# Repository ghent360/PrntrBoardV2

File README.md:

PrntrBoard V2
======================
PrntrBoard V2 is the next iteration of my 3D printer controller design. The V1 was very good, except it had one major drawback - the stepper drivers were soldered on the board which would make the design expensive.
This V2 design has 6 replaceable motor drivers. While traditional RAMPS based boards use pin headers to house the driver boards, I'm using PCIe 1x slots. This design has several advantages:
  + the driver PCB layout can be more flexible as there are fewer constraints on the driver board dimensions
  + drivers are placed vertically on the board which allows for more efficient space utilization as well as more efficient cooling
  + PCIe 1x slots have 36 pins which allows for greater design flexibility

Project Status
-----
The following functionality has been verified on the rev1 prototype board with Marlin firmware:
  + TMC2660 and TMC2209 drivers working and able to move motors
  + Endstops
  + Heaters and thermistor inputs
  + LCD interface with 12864 panel from FYSETC and REPRAP Discount Graphics Panel.
  + Micro SD-card interface
  + EEPROM
  + Fan control

Features of the board:
-----
  + up to 6x replaceable stepper motor drivers
  + 32-bit Arm processor with floating point support running at 168MHz (STM32F407)
  + up to 6 thermistors or 6 thermocouples for temperature control
  + 4 power heaters (1 bed and up to 3 extruder heaters) with PWM power control
  + 5 low power PWM connectors with selectable voltage (5V vs 12-24V) for fans or LEDs
  + 8 end stops with option to use stall detection from the stepper drivers on 6 of them
  + micro-sd card support with SDIO for fast file transfer
  + 2 extra serial ports for WiFi and or smart LCD screen control
  + RAMPS LCD screen support
  + Marlin 2.0 firmware or Smoothieware V1.0, RRF port in progress, Klipper port in progress.
  + 4 extra fan connectors (2x5V and 2x12-24V)
  + Input voltage: 12-24V
  + CAN bus connector contributed by ArkadiuszRaj.

Drivers
------
High power driver using Trinamic TMC2660. Should support up to 2.5A RMS current per phase with forced cooling. Supports stall detection. Driver current is adjustable via SPI.

Versatile "economy" driver using Trinamic TMC2209. Should support up to 1.8A RMS current per phase with forced cooling. Supports stall detection. Driver current is adjustable via UART.

High voltage driver (up to 42V) using Trinamic TMC2130. Should support up to 1.1A RMS current per phase with forced cooling. Supports stall detection. Driver current is adjustable via SPI. The driver board has separate power terminal.

Very high current driver design using TMC5161 and TMC2160 with external MOSFETS are also possible. In addition an adapter board for Pololu style stepper drivers is planned for backwards compatibility with old drivers.

Software
------

Marlin v2 is working on the board. I have a port of Smoothieware V1. Klipper is functional with some [fixes] (https://github.com/ghent360/klipper). RepRepFirmware ports is in early stages and not yet functional.

Visit [my blog](https://blog.pcbxprt.com/) for status updates on the development of the board.

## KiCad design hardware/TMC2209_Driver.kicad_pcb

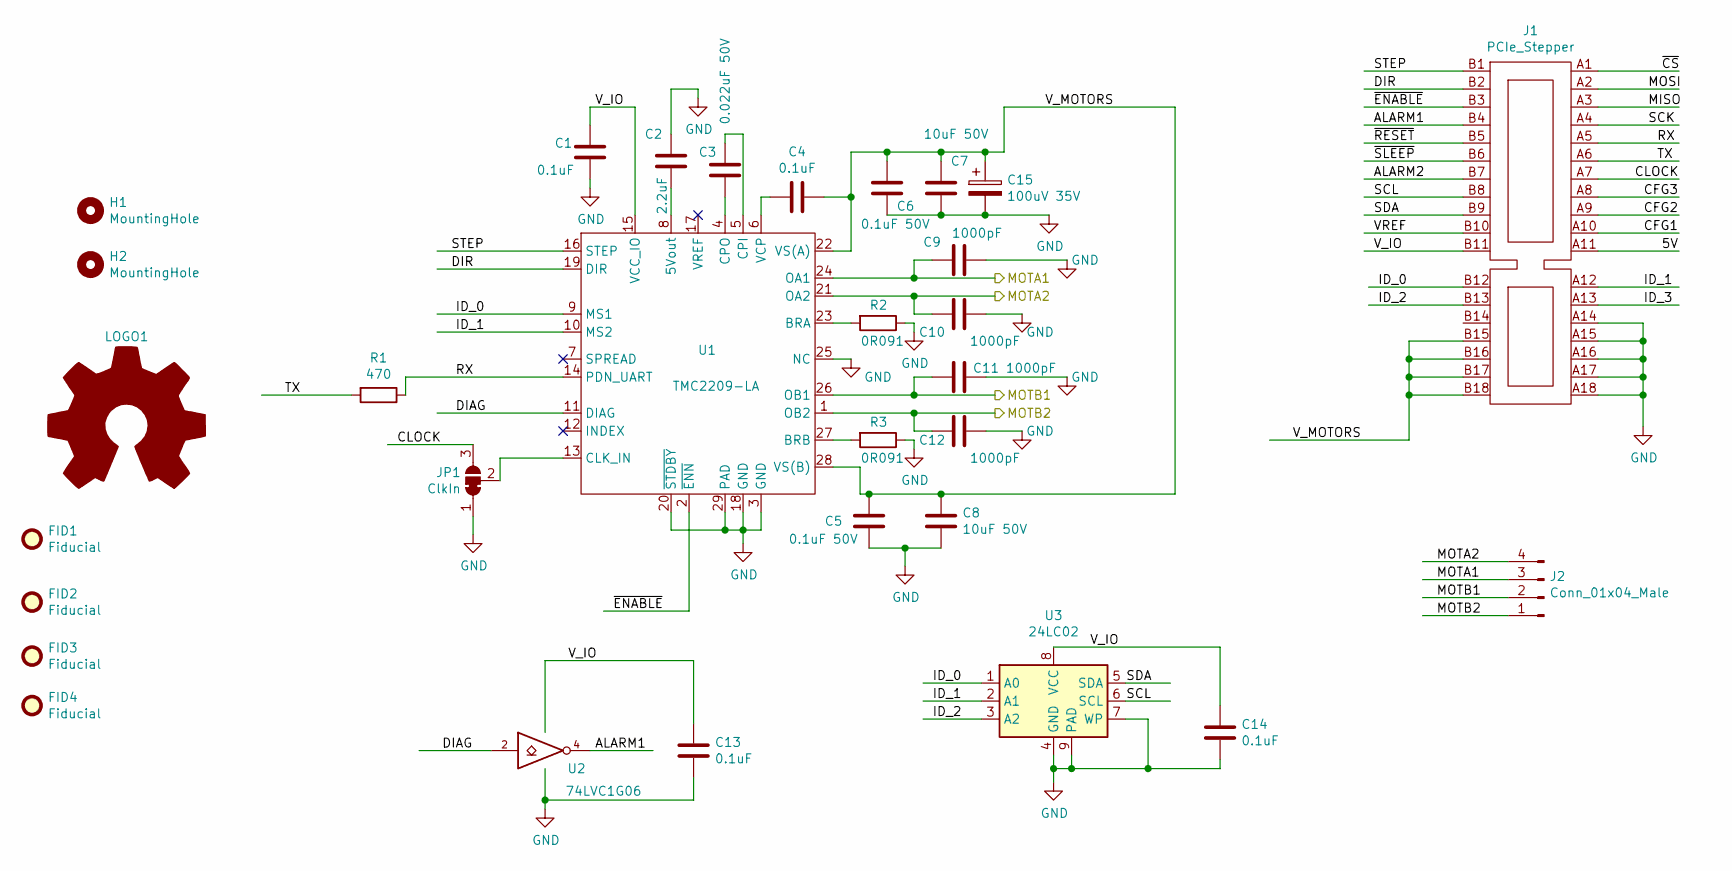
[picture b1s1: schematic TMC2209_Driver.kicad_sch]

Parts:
C1, C4, C13, C14: 0.1uF; C_0603_1608Metric; Part # CC0603KRX7R9BB104; LCSC Part # C14663
C2: 2.2uF; C_0603_1608Metric; Part # CL10A225KO8NNNC; LCSC Part # C23630
C3: 0.022uF 50V; C_0603_1608Metric; Part # CL10B223KB8NNNC; LCSC Part # C21122
C5, C6: 0.1uF 50V; C_0402_1005Metric; Part # CL05B104KO5NNNC; LCSC Part # C1525
C7, C8: 10uF 50V; C_1206_3216Metric; Part # CL31A106KBHNNNE; LCSC Part # C13585
C9, C10, C11, C12: 1000pF; C_0603_1608Metric; Part # CL10B102KB8NNNC; LCSC Part # C1588
C15: 100uV 35V; CP_Elec_6.3x7.7; Part # VE-101M1VTR-0607; LCSC Part # C171732
FID1, FID2, FID3, FID4: Fiducial; Fiducial_1mm_Dia_2.54mm_Outer_CopperTop
H1, H2: MountingHole; MountingHole_2.7mm_M2.5
J1: PCIe_Stepper; BUS_PCIexpress
J2: Conn_01x04_Male; Molex-SL-4POS
JP1: ClkIn; SolderJumper-3_P1.3mm_Bridged12_Pad1.0x1.5mm
LOGO1: Logo_Open_Hardware_Large; OSHW-Logo2_7.3x6mm_SilkScreen
R1: 470; R_0603_1608Metric; Part # 0603WAF4700T5E; LCSC Part # C23179
R2, R3: 0R091; R_1210_3225Metric; Part # 1206W3F910MT5E; LCSC Part # C247542
U1: TMC2209-LA; TMC22xx_QFN; Part # TMC2209-LA; LCSC Part # C465949
U2: 74LVC1G06; SOT-353_SC-70-5; Part # 74LVC1G06GW,125; LCSC Part # C426704
U3: 24LC02; TDFN-8-1EP_3x2mm_P0.5mm_EP1.56x1.45mm; Part # CAT24C02VP2IGT3A; LCSC Part # C184154

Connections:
/5V: J1.A11
/ALARM1: J1.B4, U2.4
/ALARM2: J1.B7
/CFG1: J1.A10
/CFG2: J1.A9
/CFG3: J1.A8
/CLOCK: J1.A7, JP1.3 (B)
/DIAG: U1.11 (DIAG), U2.2
/DIR: J1.B2, U1.19 (DIR)
/ID_0: J1.B12, U1.9 (MS1), U3.1 (A0)
/ID_1: J1.A12, U1.10 (MS2), U3.2 (A1)
/ID_2: J1.B13, U3.3 (A2)
/ID_3: J1.A13
/MISO: J1.A3
/MOSI: J1.A2
/MOTA1: C9.2, J2.3, U1.24 (OA1)
/MOTA2: C10.2, J2.4, U1.21 (OA2)
/MOTB1: C11.2, J2.2, U1.26 (OB1)
/MOTB2: C12.2, J2.1, U1.1 (OB2)
/RX: J1.A5, R1.1, U1.14 (PDN_UART)
/SCK: J1.A4
/SCL: J1.B8, U3.6 (SCL)
/SDA: J1.B9, U3.5 (SDA)
/STEP: J1.B1, U1.16 (STEP)
/TX: J1.A6, R1.2
/VREF: J1.B10
/V_MOTORS: C4.1, C5.1, C6.1, C7.1, C8.1, C15.1, J1.B15, J1.B16, J1.B17, J1.B18, U1.22 (VS(A)), U1.28 (VS(B))
/~CS: J1.A1
/~ENABLE: J1.B3, U1.2 (~ENN)
/~RESET: J1.B5
/~SLEEP: J1.B6
GND: C1.2, C2.1, C5.2, C6.2, C7.2, C8.2, C9.1, C10.1, C11.1, C12.1, C13.2, C14.2, C15.2, J1.A14, J1.A15, J1.A16, J1.A17, J1.A18, JP1.1 (A), R2.1, R3.1, U1.3 (GND), U1.18 (GND), U1.20 (~STDBY), U1.25 (NC), U1.29 (PAD), U2.3 (GND), U3.4 (GND), U3.7 (WP), U3.9 (PAD)
unnamed: C2.2, U1.8 (5Vout)
unnamed: C3.1, U1.5 (CPI)
unnamed: C3.2, U1.4 (CPO)
unnamed: C4.2, U1.6 (VCP)
unnamed: JP1.2 (C), U1.13 (CLK_IN)
unnamed: R2.2, U1.23 (BRA)
unnamed: R3.2, U1.27 (BRB)
VCC: C1.1, C13.1, C14.1, J1.B11, U1.15 (VCC_IO), U2.5 (VCC), U3.8 (VCC)

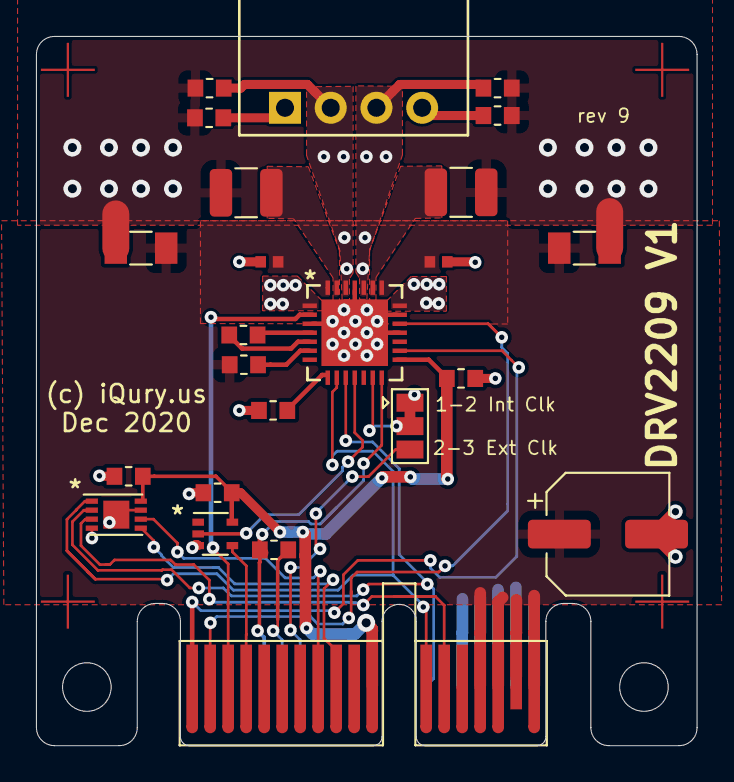
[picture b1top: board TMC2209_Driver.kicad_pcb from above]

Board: 2 copper layers, 36.7 x 39.4 mm, 31 parts (1 on the bottom side), 27 nets.

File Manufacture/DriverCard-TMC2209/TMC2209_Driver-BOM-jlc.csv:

Comment,Designator,Footprint,LCSC, LCSC Part #, Part #
"0.1uF","C1,C4,C13,C14","PrntrBoardV2:C_0603_1608Metric","","C14663","CC0603KRX7R9BB104"
"100uV 35V","C15","Capacitor_SMD:CP_Elec_6.3x7.7","","C171732","VE-101M1VTR-0607"
"2.2uF","C2","PrntrBoardV2:C_0603_1608Metric",""," C23630","CL10A225KO8NNNC"
"0.022uF 50V","C3","PrntrBoardV2:C_0603_1608Metric","","C21122","CL10B223KB8NNNC"
"0.1uF 50V","C5,C6","PrntrBoardV2:C_0402_1005Metric","","C1525","CL05B104KO5NNNC"
"10uF 50V","C7,C8","PrntrBoardV2:C_1206_3216Metric","","C13585","CL31A106KBHNNNE"
"1000pF","C9,C10,C11,C12","PrntrBoardV2:C_0603_1608Metric","","C1588","CL10B102KB8NNNC"
"Conn_01x04_Male","J2","PrntrBoardV2:Molex-SL-4POS",""
"470","R1","PrntrBoardV2:R_0603_1608Metric","","C23179","0603WAF4700T5E"
"0R091","R2,R3","Resistor_SMD:R_1210_3225Metric","","C247542","1206W3F910MT5E"
"TMC2209-LA","U1","PrntrBoardV2:TMC22xx_QFN","","C465949","TMC2209-LA"
"74LVC1G06","U2","Package_TO_SOT_SMD:SOT-353_SC-70-5","","C426704","74LVC1G06GW,125"
"24LC02","U3","PrntrBoardV2:TDFN-8-1EP_3x2mm_P0.5mm_EP1.56x1.45mm","","C184154","CAT24C02VP2IGT3A"

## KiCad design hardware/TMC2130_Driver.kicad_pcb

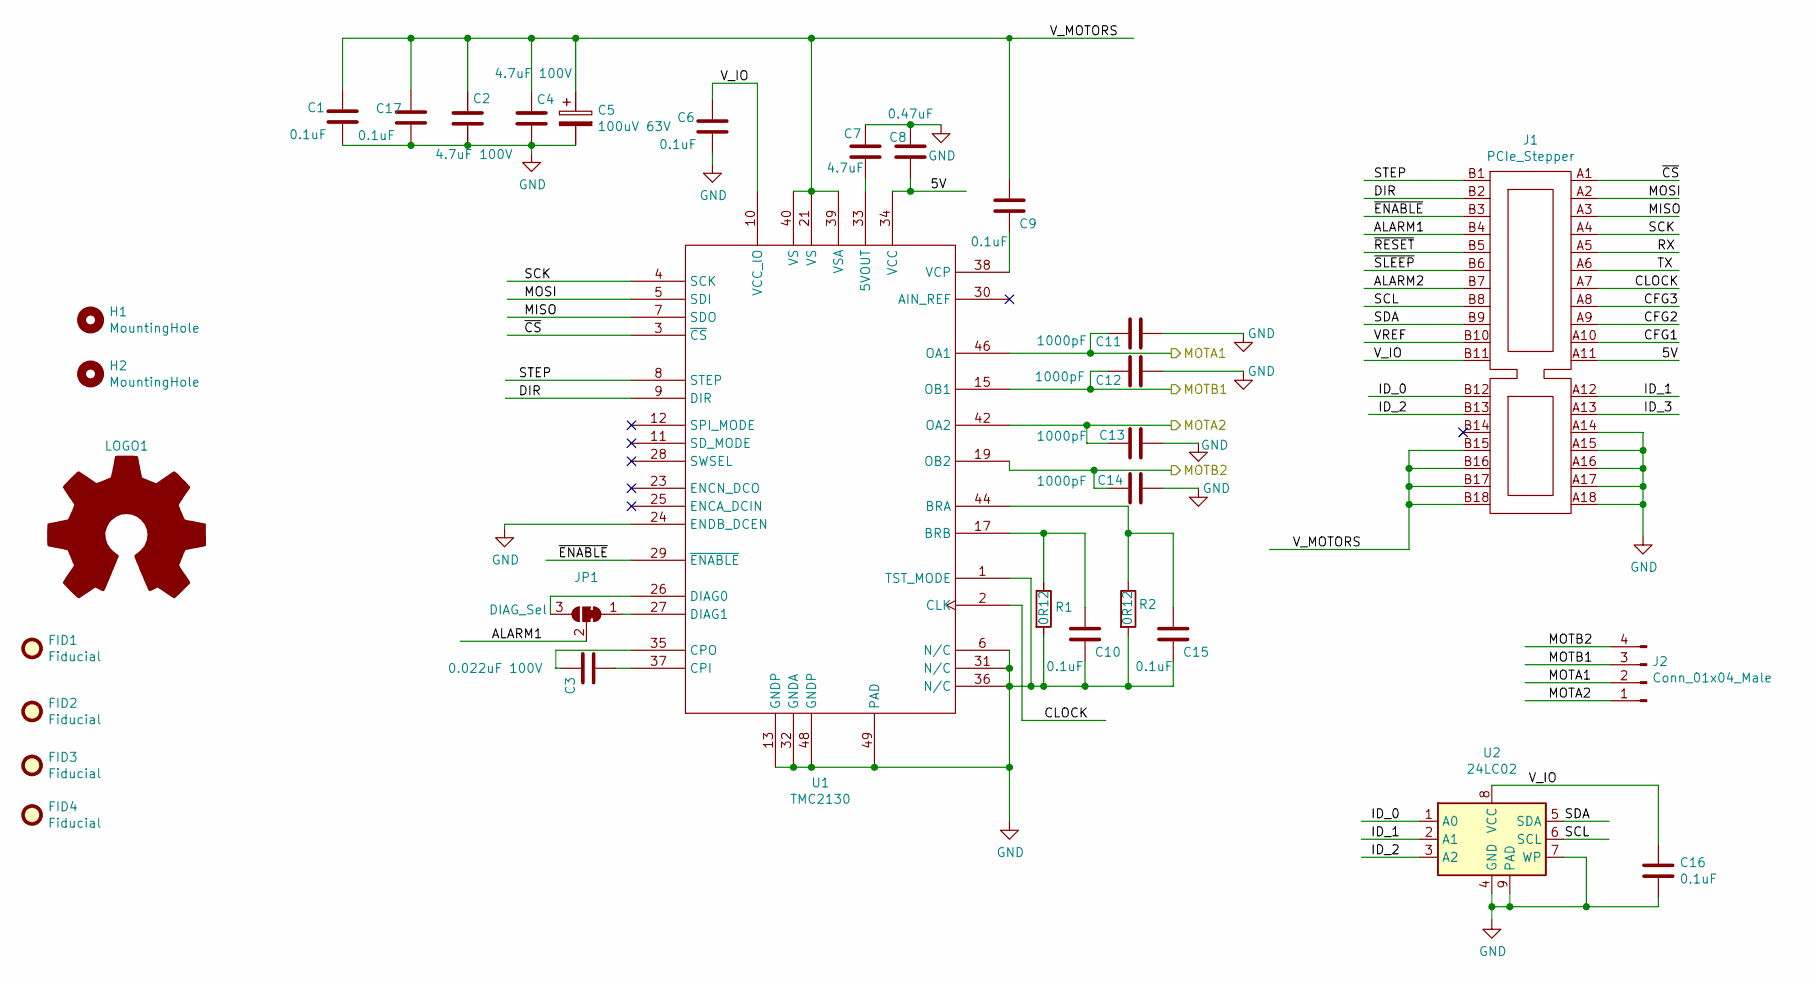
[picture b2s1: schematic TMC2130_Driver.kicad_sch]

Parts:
C1, C9, C17: 0.1uF; C_0805_2012Metric; Part # CL21B104KCFNNNE; LCSC Part # C28233
C2, C4: 4.7uF 100V; C_1210_3225Metric; Part # HMK325C7475KN-TE; LCSC Part # C697607
C3: 0.022uF 100V; C_0805_2012Metric; Part # CC0603KRX7R0BB223; LCSC Part # C313105
C5: 100uV 63V; CP_Elec_10x10.5; Part # CK1J101MCRG10; LCSC Part # C263945
C6, C16: 0.1uF; C_0603_1608Metric; Part # CC0603KRX7R9BB104; LCSC Part # C14663
C7: 4.7uF; C_0603_1608Metric; Part # CL10A475KO8NNNC; LCSC Part # C19666
C8: 0.47uF; C_0603_1608Metric; Part # CL10B474KA8NNNC; LCSC Part # C1623
C10, C15: 0.1uF; C_0805_2012Metric; Part # HMK325C7475KN-TE; LCSC Part # C28233
C11, C12, C13, C14: 1000pF; C_0603_1608Metric; Part # CL10B102KC8NNNC; LCSC Part # C153291
FID1, FID2, FID3, FID4: Fiducial; Fiducial_1mm_Dia_2.54mm_Outer_CopperTop
H1, H2: MountingHole; MountingHole_2.7mm_M2.5
J1: PCIe_Stepper; BUS_PCIexpress
J2: Conn_01x04_Male; Molex-SL-4POS
JP1: DIAG_Sel; SolderJumper-3_P1.3mm_Bridged12_Pad1.0x1.5mm
LOGO1: Logo_Open_Hardware_Large; OSHW-Logo2_7.3x6mm_SilkScreen
R1, R2: 0R12; R_2512_6332Metric; Part # 25121WF120LT4E; LCSC Part # C81248
U1: TMC2130; tmc5130-nc; Part # TMC2130A-TA; LCSC Part # C328952
U2: 24LC02; TDFN-8-1EP_3x2mm_P0.5mm_EP1.56x1.45mm; Part # CAT24C02VP2IGT3A; LCSC Part # C184154

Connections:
/5V: C8.1, J1.A11, U1.34 (VCC)
/ALARM1: J1.B4, JP1.2 (C)
/ALARM2: J1.B7
/CFG1: J1.A10
/CFG2: J1.A9
/CFG3: J1.A8
/CLOCK: J1.A7, U1.2 (CLK)
/DIR: J1.B2, U1.9 (DIR)
/ID_0: J1.B12, U2.1 (A0)
/ID_1: J1.A12, U2.2 (A1)
/ID_2: J1.B13, U2.3 (A2)
/ID_3: J1.A13
/MISO: J1.A3, U1.7 (SDO)
/MOSI: J1.A2, U1.5 (SDI)
/MOTA1: C11.2, J2.2, U1.46 (OA1)
/MOTA2: C13.2, J2.1, U1.42 (OA2)
/MOTB1: C12.2, J2.3, U1.15 (OB1)
/MOTB2: C14.2, J2.4, U1.19 (OB2)
/RX: J1.A5
/SCK: J1.A4, U1.4 (SCK)
/SCL: J1.B8, U2.6 (SCL)
/SDA: J1.B9, U2.5 (SDA)
/STEP: J1.B1, U1.8 (STEP)
/TX: J1.A6
/VREF: J1.B10
/V_IO: C6.1, C16.1, J1.B11, U1.10 (VCC_IO), U2.8 (VCC)
/V_MOTORS: C1.1, C2.1, C4.1, C5.1, C9.1, C17.1, J1.B15, J1.B16, J1.B17, J1.B18, U1.21 (VS), U1.39 (VSA), U1.40 (VS)
/~CS: J1.A1, U1.3 (~CS)
/~ENABLE: J1.B3, U1.29 (~ENABLE)
/~RESET: J1.B5
/~SLEEP: J1.B6
GND: C1.2, C2.2, C4.2, C5.2, C6.2, C7.1, C8.2, C10.2, C11.1, C12.1, C13.1, C14.1, C15.2, C16.2, C17.2, J1.A14, J1.A15, J1.A16, J1.A17, J1.A18, R1.2, R2.2, U1.1 (TST_MODE), U1.6 (N/C), U1.13 (GNDP), U1.24 (ENDB_DCEN), U1.31 (N/C), U1.32 (GNDA), U1.36 (N/C), U1.48 (GNDP), U1.49 (PAD), U2.4 (GND), U2.7 (WP), U2.9 (PAD)
unnamed: C3.1, U1.35 (CPO)
unnamed: C3.2, U1.37 (CPI)
unnamed: C7.2, U1.33 (5VOUT)
unnamed: C9.2, U1.38 (VCP)
unnamed: C10.1, R1.1, U1.17 (BRB)
unnamed: C15.1, R2.1, U1.44 (BRA)
unnamed: JP1.1 (A), U1.27 (DIAG1)
unnamed: JP1.3 (B), U1.26 (DIAG0)

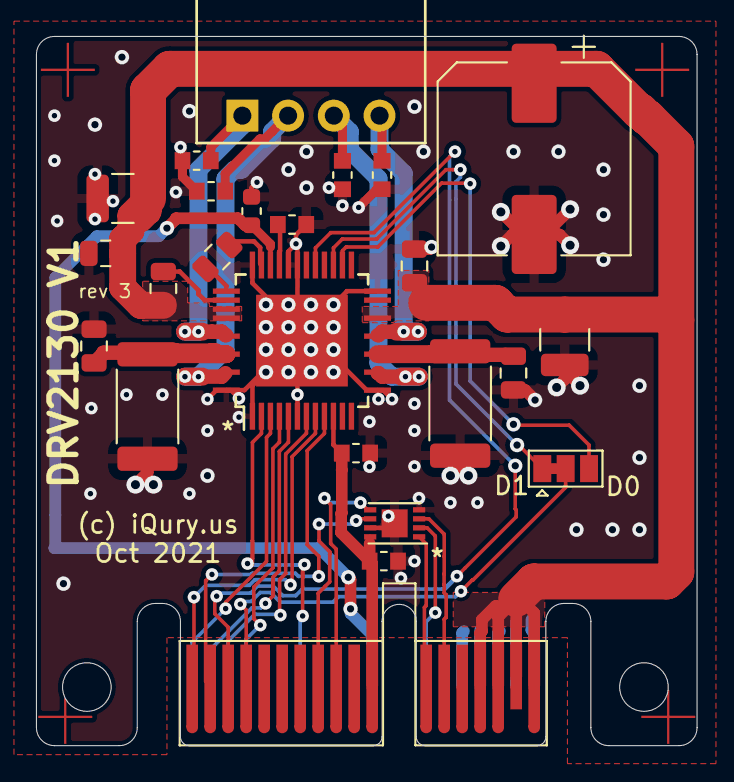
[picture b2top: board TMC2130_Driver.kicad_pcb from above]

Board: 2 copper layers, 36.7 x 39.4 mm, 31 parts (1 on the bottom side), 30 nets.

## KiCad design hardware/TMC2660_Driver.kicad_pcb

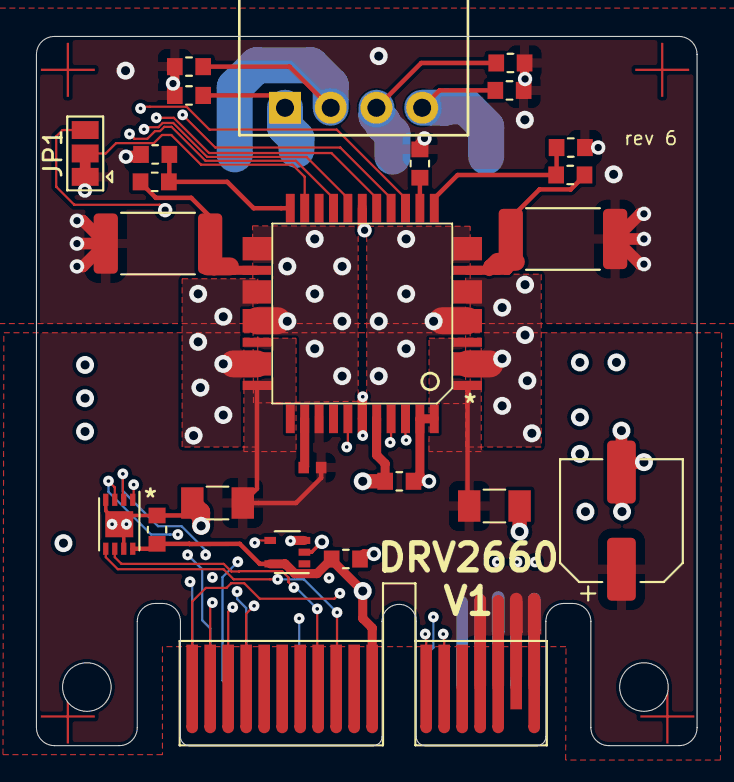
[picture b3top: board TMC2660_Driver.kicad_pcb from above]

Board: 4 copper layers, 36.7 x 39.4 mm, 31 parts (1 on the bottom side), 29 nets.

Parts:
C1, C2: 10uF 50V; C_1206_3216Metric
C3, C6, C14: 0.1uF; C_0603_1608Metric
C4: 0.1uF 50V; C_0402_1005Metric
C5: 0.47uF; C_0603_1608Metric
C7, C12: 0.01uF; C_0603_1608Metric
C8, C9, C10, C11: 1000pF; C_0603_1608Metric
C13: 100uF 35V; CP_Elec_6.3x7.7
FID1, FID2, FID3, FID4: Fiducial; Fiducial_1mm_Dia_2.54mm_Outer_CopperTop
H1, H2: MountingHole; MountingHole_2.7mm_M2.5
J1: PCIe_Stepper; BUS_PCIexpress
J2: Conn_01x04_Male; Molex-SL-4POS
JP1: ClkIn; SolderJumper-3_P1.3mm_Bridged12_Pad1.0x1.5mm
LOGO1: Logo_Open_Hardware_Large; OSHW-Logo2_7.3x6mm_SilkScreen
R1, R3: 22R; R_0603_1608Metric
R2, R4: 0R051; R_2512_6332Metric
U1: TMC2660
U2: 74LVC1G06; SOT-353_SC-70-5
U3: 24LC02; TDFN-8-1EP_3x2mm_P0.5mm_EP1.56x1.45mm

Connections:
/ALARM1: J1.B4, U2.4
/CLOCK: J1.A7, JP1.3 (B)
/DIAG: U1.38 (SG_TST), U2.2
/DIR: J1.B2, U1.41 (DIR)
/ID_0: J1.B12, U3.1 (A0)
/ID_1: J1.A12, U3.2 (A1)
/ID_2: J1.B13, U3.3 (A2)
/MISO: J1.A3, U1.15 (SDI)
/MOSI: J1.A2, U1.14 (SDO)
/MOTA1: C8.2, J2.4, U1.2.3 (OA1), U1.7.8 (OA1)
/MOTA2: C9.2, J2.3, U1.5.6 (OA2), U1.10.1 (OA2)
/MOTB1: C10.2, J2.2, U1.26.7 (OB1), U1.31.2 (OB1)
/MOTB2: C11.2, J2.1, U1.23.4 (OB2), U1.28.9 (OB2)
/SCK: J1.A4, U1.16 (SCK)
/SCL: J1.B8, U3.6 (SCL)
/SDA: J1.B9, U3.5 (SDA)
/STEP: J1.B1, U1.42 (STEP)
/V_MOTORS: C1.1, C2.1, C4.1, C13.1, J1.B15, J1.B16, J1.B17, J1.B18, U1.1 (NC), U1.4 (VSA), U1.30 (VSB), U1.33 (NC), U1.36 (VS)
/~CS: J1.A1, U1.18 (~CS)
/~ENABLE: J1.B3, U1.19 (~EN)
GND: C1.2, C2.2, C3.2, C5.1, C6.2, C7.2, C8.1, C9.1, C10.1, C11.1, C12.2, C13.2, C14.2, J1.A14, J1.A15, J1.A16, J1.A17, J1.A18, JP1.1 (A), R2.2, R4.2, U1.17 (GND), U1.39 (GND), U1.43 (TST_MODE), U1.44 (GND), U2.3 (GND), U3.4 (GND), U3.7 (WP), U3.9 (PAD)
unnamed: C4.2, U1.35 (VHS)
unnamed: C5.2, U1.13 (5VOUT)
unnamed: C7.1, R1.1, U1.22 (SRB)
unnamed: C12.1, R3.1, U1.12 (SRA)
unnamed: R1.2, R2.1, U1.25 (BRB)
unnamed: R3.2, R4.1, U1.9 (BRA)
unnamed: JP1.2 (C), U1.21 (CLK)
VCC: C3.1, C6.1, C14.1, J1.B11, U1.40 (VCC_IO), U2.5 (VCC), U3.8 (VCC)

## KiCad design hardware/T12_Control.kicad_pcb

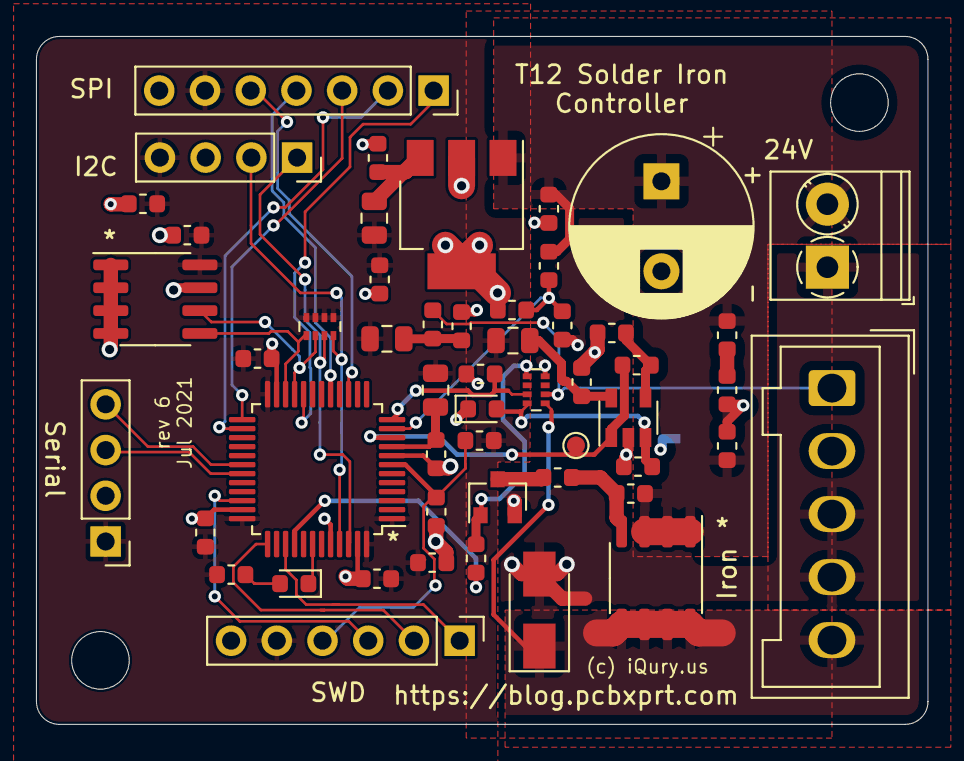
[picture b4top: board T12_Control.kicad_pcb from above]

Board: 4 copper layers, 49.5 x 38.2 mm, 55 parts (1 on the bottom side), 37 nets.

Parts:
C1, C2, C3, C4, C6, C7, C8, C9, C11, C13, C14, C17: 100nF; C_0603_1608Metric
C5: 10uF; C_0603_1608Metric
C10, C18: 10nF; C_0603_1608Metric
C12: 100uF 35V; CP_Radial_D10.0mm_P5.00mm
C15: 1nF; C_0603_1608Metric
C16: 470pF; C_0603_1608Metric
C19: 1uF; C_0603_1608Metric
D1: RS1M; D_SMA
D2, D3: RED; LED_0603_1608Metric
FB1, FB2, FB3, FB4: Ferrite_Bead; L_0805_2012Metric
H1, H2: MountingHole; MountingHole_3.2mm_M3_DIN965
J1: Screw_Terminal_01x02; TerminalBlock_Phoenix_PT-1,5-2-3.5-H_1x02_P3.50mm_Horizontal
J2: GX12-5M; Wago_734-135_1x05_P3.50mm_Vertical
J3: SPI LCD; PinSocket_1x07_P2.54mm_Vertical
J4: I2C LCD; PinSocket_1x04_P2.54mm_Vertical
J5: SWD; PinHeader_1x06_P2.54mm_Vertical
J6: Serial; PinHeader_1x04_P2.54mm_Vertical
NT1: Net-Tie_2; NetTie-2_SMD_Pad0.5mm
Q1: TPC8107; SO-8_3.9x4.9mm_P1.27mm
Q2: BC817; SOT-23
R1: 2k; R_0603_1608Metric
R2, R7: 10k; R_0603_1608Metric
R3, R4, R9: 1k; R_0603_1608Metric
R5: 1k 0.1%; R_0603_1608Metric
R6: 249k 0.1%; R_0603_1608Metric
R8: 470; R_0603_1608Metric
R10: 2.2; R_0603_1608Metric
R11: 4.7k 1%; R_0603_1608Metric
RN1, RN2: 4x4.7k; R_Array_Concave_4x0402
TP1: TestPoint; TestPoint_Pad_D1.0mm
U1: SPX2954M3-3.3_SOT223; SOT-223-3_TabPin2
U2: 24LC32; SOIC-8_3.9x4.9mm_P1.27mm
U3: SGM8551XN; SOT-23-5
U4: STM32F103CBTx; LQFP-48_7x7mm_P0.5mm

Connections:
/3.3V: C3.1, C6.1, C7.1, C8.1, C9.1, C14.1, C17.1, FB1.2, FB2.1, FB3.1, FB4.1, J3.6, J4.4, J5.5, J6.1, R7.1, R9.2, RN2.1 (R1.1), RN2.2 (R2.1), RN2.3 (R3.1), RN2.4 (R4.1), U2.8 (VCC), U4.1 (VBAT), U4.24 (VDD), U4.36 (VDD), U4.48 (VDD)
/24V: C1.1, C2.1, C12.1, J1.2, Q1.1 (S), Q1.2 (S), Q1.3 (S), R1.1, R2.1, R10.1, U1.1 (VI)
/D/~C: J3.2, U4.26 (PB13)
/EE_SCL: RN2.6 (R3.2), U2.6 (SCL), U4.21 (PB10)
/EE_SDA: RN2.5 (R4.2), U2.5 (SDA), U4.22 (PB11)
/HEATER_ON: R8.2, U4.40 (PB4)
/MOSI: J3.4, U4.17 (PA7)
/NTC: C19.1, RN1.3 (R3.1), U4.12 (PA2)
/OLED_SCL: J4.2, RN2.8 (R1.2), U4.45 (PB8)
/OLED_SDA: J4.1, RN2.7 (R2.2), U4.46 (PB9)
/RX: J6.3, U4.31 (PA10)
/SCK: J3.5, U4.15 (PA5)
/SWDCLK: J5.2, U4.37 (PA14)
/SWDIO: J5.3, U4.34 (PA13)
/SWDSWO: J5.1, U4.39 (PB3)
/TIP_TEMP: R6.2, TP1.1, U3.1, U4.10 (PA0)
/TX: J6.4, U4.30 (PA9)
/V_MON: C4.1, R2.2, R4.1, U4.11 (PA1)
/~CS: J3.1, U4.20 (PB2)
/~NRST: C11.2, J5.4, R7.2, U4.7 (NRST)
/~RST: J3.3, U4.25 (PB12)
GND: C1.2, C2.2, C3.2, C4.2, C5.2, C6.2, C7.2, C8.2, C9.2, C11.1, C12.2, C14.2, C16.2, C17.2, C19.2, D1.2 (A), J1.1, J2.3, J2.4, J3.7, J4.3, J5.6, J6.2, NT1.2, Q2.2 (E), R4.2, RN1.8 (R1.2), U1.2 (GND), U2.1 (A0), U2.2 (A1), U2.3 (A2), U2.4 (GND), U2.7 (WP), U4.23 (VSS), U4.35 (VSS), U4.44 (BOOT0), U4.47 (VSS)
GNDA: C10.2, C13.2, C15.2, C18.2, D2.1 (K), NT1.1, R5.2, U3.2 (V-), U4.8 (VSSA)
unnamed: C5.1, FB1.1, U1.3 (VO)
unnamed: C10.1, FB2.2, U4.9 (VDDA)
unnamed: C13.1, FB3.2, U3.5 (V+)
unnamed: C15.1, D2.2 (A), RN1.4 (R4.1), U3.3 (+)
unnamed: C16.1, R10.2
unnamed: C18.1, FB4.2, R11.2
unnamed: D1.1 (K), J2.5, Q1.5 (D), Q1.6 (D), Q1.7 (D), Q1.8 (D), RN1.5 (R4.2)
unnamed: D3.1 (K), U4.42 (PB6)
unnamed: D3.2 (A), R9.1
unnamed: J2.1, R11.1, RN1.6 (R3.2)
unnamed: Q1.4 (G), R1.2, R3.1
unnamed: Q2.1 (B), R8.1, RN1.1 (R1.1)
unnamed: Q2.3 (C), R3.2
unnamed: R5.1, R6.1, U3.4 (-)

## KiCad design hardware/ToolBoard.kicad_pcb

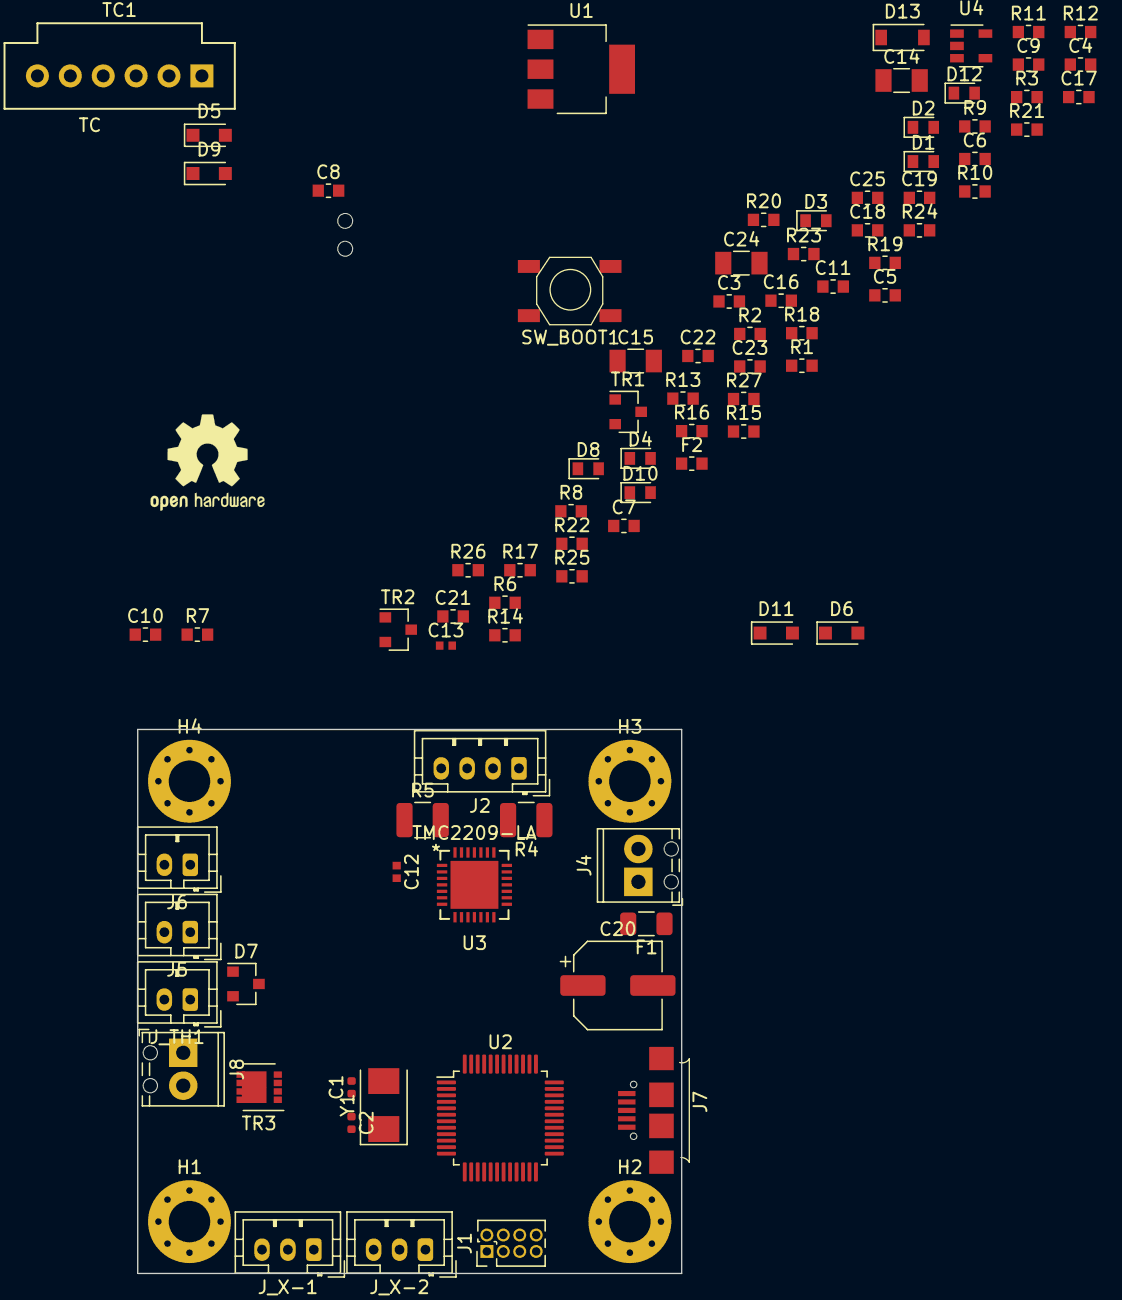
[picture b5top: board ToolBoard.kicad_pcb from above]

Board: 2 copper layers, 42.0 x 42.0 mm, 94 parts (0 on the bottom side), 55 nets, no tracks yet.

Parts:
C1, C2: 22pF; C_0402_1005Metric
C3, C5, C6, C8, C11, C25: 0.1uF; C_0603_1608Metric
C4, C7: 10uF; C_0603_1608Metric
C9: 2.2uF; C_0603_1608Metric
C10: 0.022uF 50V; C_0603_1608Metric
C12, C13: 0.1uF 50V; C_0402_1005Metric
C14, C15, C24: 10uF 50V; C_1206_3216Metric
C16, C17, C18, C19, C21, C22, C23: 1000pF; C_0603_1608Metric
C20: 100uV 35V; CP_Elec_6.3x7.7
D1, D2, D3, D4, D8, D10, D12: LED; LED_0603_1608Metric
D5, D6, D9, D11: 1N4148; D_SOD-323_HandSoldering
D7: BAT54S; SOT-23
D13: B5819W; D_SOD-123
F1: Fuse; Fuse_1206_3216Metric
F2: 500mA; R_0603_1608Metric
H1, H2, H3, H4: MountingHole; MountingHole_3.2mm_M3_Pad_Via
J1: DBG; PinHeader_2x04_P1.27mm_Vertical
J2: Conn_01x04_Male; JST_PH_B4B-PH-K_1x04_P2.00mm_Vertical
J4, J8: KF350; TerminalBlock_Phoenix_MPT-0,5-2-2.54_1x02_P2.54mm_Horizontal
J5, J6: JST XH; JST_PH_B2B-PH-K_1x02_P2.00mm_Vertical
J7: USB_B_Micro; MC-101C
J_TH1: JST XH; JST_PH_B2B-PH-K_1x02_P2.00mm_Vertical
J_X-1, J_X-2: JST XH 3p; JST_PH_B3B-PH-K_1x03_P2.00mm_Vertical
LOGO1: Logo_Open_Hardware_Small; OSHW-Logo2_9.8x8mm_SilkScreen
R1, R2, R6, R7, R11, R14, R16, R17, R19, R21, R23: 10k; R_0603_1608Metric
R3, R9, R15, R20: 470; R_0603_1608Metric
R4, R5: 0R091; R_1210_3225Metric
R8, R10, R12, R18: 1k; R_0603_1608Metric
R13: 4k7; R_0603_1608Metric
R22: 180; R_0603_1608Metric
R24: 1.5k; R_0603_1608Metric
R25, R26: 22; R_0603_1608Metric
R27: 100k; R_0603_1608Metric
SW_BOOT1: SW_Push; Button_4x4
TC1: TC; Molex-SL-6POS
TH1, TH2: JLC Tooling Hole; JLC_Tool_hole
TR1, TR2: SI2318CDS; SOT-23
TR3: PSMN7R0-30YL; VSON-8_3.3x3.3mm_P0.65mm_NexFET
U1: AMS1117-3.3; SOT-223-3_TabPin2
U2: STM32F103C8Tx; LQFP-48_7x7mm_P0.5mm
U3: TMC2209-LA; TMC22xx_QFN
U4: 74AHCT1G14; SOT-23-5
Y1: 8MHz; Crystal_SMD_5032-2Pin_5.0x3.2mm

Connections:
3.3V: C6.1, C7.1, C8.1, J1.8, R8.1, R9.1, R15.1, R19.1, R20.1, R24.2, U1.2 (VO), U3.15 (VCC_IO)
5V: C4.1, C5.1, F2.2, J_X-1.3, J_X-2.3, R10.1, TC1.2, U1.3 (VI), U4.5 (VCC)
/BOOT: J1.5, SW_BOOT1.2
/D+: J7.3 (D+), R24.1, R26.1, U2.33 (PA12)
/D-: J7.2 (D-), R25.1, U2.32 (PA11)
/MOTA1: C16.2, J2.3, U3.24 (OA1)
/MOTA2: C17.2, J2.4, U3.21 (OA2)
/MOTB1: C18.2, J2.2, U3.26 (OB1)
/MOTB2: C19.2, J2.1, U3.1 (OB2)
/ST_UART: R3.2, U2.12 (PA2)
/SWDCLK: J1.2, U2.37 (PA14)
/SWDIO: J1.4, U2.34 (PA13)
/UART_RX: J1.1, U2.31 (PA10)
/UART_TX: J1.3, U2.30 (PA9)
/V_motors: C11.1, C13.1, C14.1, C20.1, C24.1, D6.1 (K), D11.1 (K), D13.1 (K), F1.2, J5.1, J6.1, J8.1, R7.1, R23.1, U3.22 (VS(A))
/~RST: C3.1, J1.6, R2.2, U2.7 (NRST)
ADC1: C22.1, D7.3 (common), R14.1, TC1.6, U2.10 (PA0)
AVREF: D7.2 (K), R13.1
FAN1: R11.1, R12.2, U2.21 (PB10)
FAN2: R17.1, R18.2, U2.22 (PB11)
GND: C1.1, C2.1, C3.2, C4.2, C6.2, C7.2, C8.2, C9.1, C12.2, C13.2, C14.2, C15.2, C16.1, C17.1, C18.1, C19.1, C20.2, C21.2, C22.2, C23.2, C24.2, C25.1, D1.1 (K), D2.1 (K), D3.1 (K), D4.1 (K), D7.1 (A), J1.7, J4.1, J7.5 (GND), J_TH1.2, J_X-1.2, J_X-2.2, R1.2, R4.1, R5.1, R11.2, R17.2, R27.1, TC1.1, TR1.S, TR2.S, TR3.S, U1.1 (GND), U3.3 (GND), U3.9 (MS1), U3.10 (MS2), U3.13 (CLK_IN), U3.18 (GND), U3.20 (~STDBY), U3.25 (NC), U3.29 (PAD), U4.3 (GND)
HEATER: R19.2, U2.46 (PB9), U4.2
unnamed: C1.2, U2.5 (PD0), Y1.2
unnamed: C2.2, U2.6 (PD1), Y1.1
unnamed: C9.2, U3.8 (5Vout)
unnamed: C10.1, U3.5 (CPI)
unnamed: C10.2, U3.4 (CPO)
unnamed: C11.2, U3.6 (VCP)
unnamed: C12.1, C15.1, U3.28 (VS(B))
unnamed: C21.1, D5.1 (K), J_X-1.1
unnamed: C23.1, D9.1 (K), J_X-2.1
unnamed: C25.2, J7.6 (Shield), R27.2
unnamed: D1.2 (A), R6.2
unnamed: D2.2 (A), R7.2
unnamed: D3.2 (A), R9.2
unnamed: D4.2 (A), R10.2
unnamed: D5.2 (A), D8.1 (K), R16.2
unnamed: D8.2 (A), R15.2
unnamed: D9.2 (A), D10.1 (K), R21.2
unnamed: D10.2 (A), R20.2
unnamed: D12.1 (K), D13.2 (A), J8.2, TR3.D
unnamed: D12.2 (A), R23.2
unnamed: F1.1, J4.2
unnamed: F2.1, J7.1 (VBUS)
unnamed: D11.2 (A), J6.2, TR2.D
unnamed: J_TH1.1, R13.2, R14.2
unnamed: R1.1, U2.44 (BOOT0)
unnamed: R3.1, U3.14 (PDN_UART)
unnamed: R4.2, U3.23 (BRA)
unnamed: R5.2, U3.27 (BRB)
unnamed: R8.2, SW_BOOT1.1
unnamed: R12.1, TR1.G
unnamed: R18.1, TR2.G
unnamed: R22.1, TR3.G
unnamed: R22.2, U4.4

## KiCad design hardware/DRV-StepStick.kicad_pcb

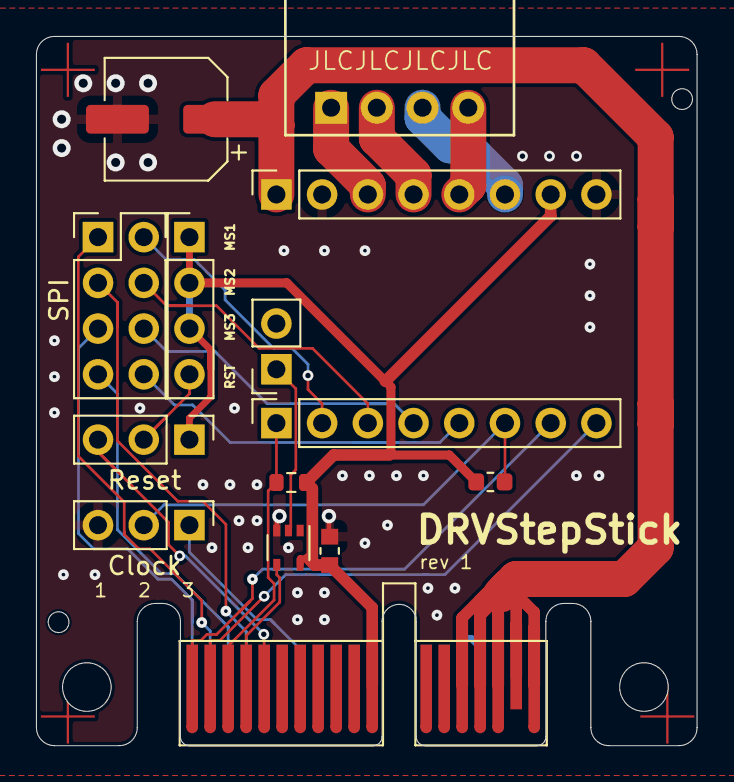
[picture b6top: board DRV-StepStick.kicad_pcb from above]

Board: 2 copper layers, 36.7 x 39.4 mm, 23 parts (1 on the bottom side), 24 nets.

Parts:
C3: 0.1uF; C_0603_1608Metric
C4: 100uF 35V; CP_Elec_6.3x7.7
FID1, FID2, FID3, FID4: Fiducial; Fiducial_1mm_Dia_2.54mm_Outer_CopperTop
H1, H2: MountingHole; MountingHole_2.7mm_M2.5
H3, H4: JLC Tooling Hole; JLC_Tool_hole
J1: PCIe_Stepper; BUS_PCIexpress
J2: Motor; Molex-SL-4POS
J3: StepStickL; PinSocket_1x08_P2.54mm_Vertical
J4: StepStickR; PinSocket_1x08_P2.54mm_Vertical
J5: Conn_01x04; PinHeader_1x04_P2.54mm_Vertical
J6: SPI Mode; PinHeader_2x04_P2.54mm_Vertical
J7: Conn_01x02; PinSocket_1x02_P2.54mm_Vertical
JP3: Clock/Sleep; PinHeader_1x03_P2.54mm_Vertical
JP4: Reset; PinHeader_1x03_P2.54mm_Vertical
LOGO1: Logo_Open_Hardware_Large; OSHW-Logo2_7.3x6mm_SilkScreen
R1, R2: 10k; R_0603_1608Metric
U2: 74LVC1G06; SOT-353_SC-70-5

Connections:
/ALARM1: J1.B4, U2.4
/CLOCK: J1.A7, JP3.1 (A)
/DIAG: J7.1, U2.2
/DIR: J1.B2, J3.8
/MISO: J1.A3, J6.7
/MOSI: J1.A2, J6.1
/MOTA1: J2.4, J4.5
/MOTA2: J2.3, J4.6
/MOTB1: J2.2, J4.4
/MOTB2: J2.1, J4.3
/MS1/MOSI: J3.2, J6.2
/MS2/SCK: J3.3, J6.4
/MS3/~CS/UART: J3.4, J6.6
/RST/MISO/UART: J3.5, J6.8
/SCK: J1.A4, J6.3
/SLP/DCO/CLK/UART: J3.6, JP3.2 (C), R2.1
/STEP: J1.B1, J3.7
/VBB: C4.1, J1.B14, J1.B15, J1.B16, J1.B17, J1.B18, J4.1
/~CS: J1.A1, J6.5
/~ENABLE: J1.B3, J3.1, R1.2
/~ST_RESET: J1.B5, JP4.3 (B)
GND: C3.2, C4.2, J1.A14, J1.A15, J1.A16, J1.A17, J1.A18, J4.2, J4.8, JP3.3 (B), U2.3 (GND)
unnamed: J5.4, JP4.2 (C)
VCC: C3.1, J1.B11, J4.7, J5.1, J5.2, J5.3, JP4.1 (A), R1.1, R2.2, U2.5 (VCC)

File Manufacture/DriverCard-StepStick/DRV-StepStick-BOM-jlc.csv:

Comment,Designator,Footprint,LCSC, LCSC Part #, Part #
"0.1uF","C3","PrntrBoardV2:C_0603_1608Metric","","C14663","CC0603KRX7R9BB104"
"100uF 35V","C4","Capacitor_SMD:CP_Elec_6.3x7.7","","C134792","VES101M1VTR-0607"
"PCIe_Stepper","J1","Connector_PCBEdge:BUS_PCIexpress",""
"Motor","J2","PrntrBoardV2:Molex-SL-4POS",""
"StepStickL","J3","Connector_PinSocket_2.54mm:PinSocket_1x08_P2.54mm_Vertical",""
"StepStickR","J4","Connector_PinSocket_2.54mm:PinSocket_1x08_P2.54mm_Vertical",""
"Conn_01x04","J5","Connector_PinHeader_2.54mm:PinHeader_1x04_P2.54mm_Vertical",""
"SPI Mode","J6","Connector_PinHeader_2.54mm:PinHeader_2x04_P2.54mm_Vertical",""
"Conn_01x02","J7","Connector_PinSocket_2.54mm:PinSocket_1x02_P2.54mm_Vertical",""
"Clock/Sleep","JP3","Connector_PinHeader_2.54mm:PinHeader_1x03_P2.54mm_Vertical",""
"Reset","JP4","Connector_PinHeader_2.54mm:PinHeader_1x03_P2.54mm_Vertical",""
"10k","R1,R2","Resistor_SMD:R_0603_1608Metric","","C29718","4D03WGJ0103T5E"
"74LVC1G06","U2","Package_TO_SOT_SMD:SOT-353_SC-70-5","","C7828","SN74LVC1G06DCKR"

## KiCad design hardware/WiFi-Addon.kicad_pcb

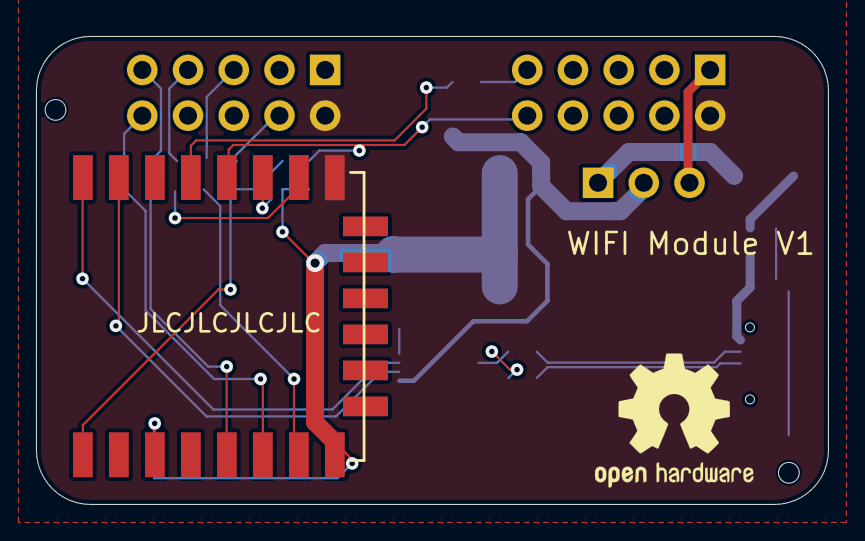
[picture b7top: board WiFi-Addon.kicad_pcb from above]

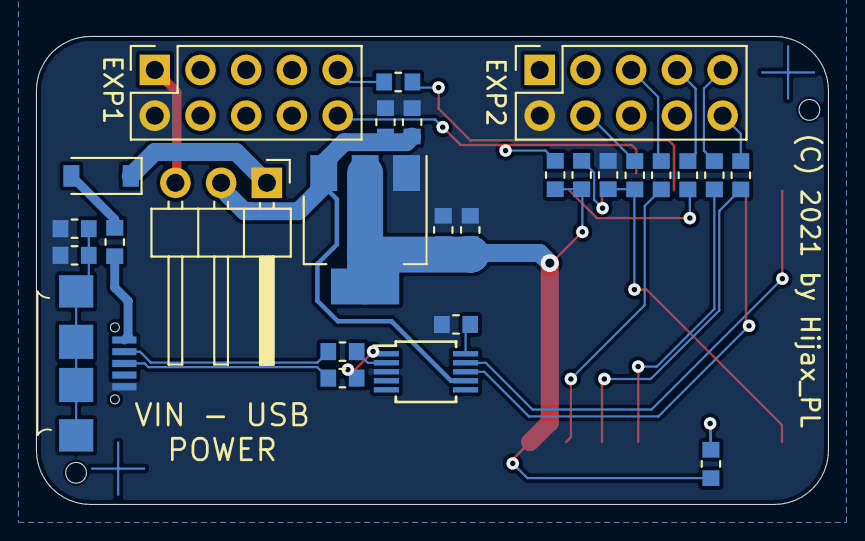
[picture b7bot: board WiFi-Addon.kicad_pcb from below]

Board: 2 copper layers, 44.0 x 26.0 mm, 33 parts (29 on the bottom side), 30 nets.

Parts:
C1, C4: 10uF; C_0603_1608Metric
C2, C3, C5, C19: 0.1uF; C_0603_1608Metric
C6: 10n; C_0603_1608Metric
D1: B5819W; D_SOD-123
EXP1, EXP2: IDC 2x5; PinSocket_2x05_P2.54mm_Vertical
F1: 500mA; R_0603_1608Metric
FID1, FID2: Fiducial; Fiducial_1mm_Dia_2.54mm_Outer_CopperTop
H1, H2: JLC Tooling Hole; JLC_Tool_hole
J1: PWR; PinHeader_1x03_P2.54mm_Horizontal
J3: USB_B_Micro; MC-101C
LOGO1: Logo_Open_Hardware_Small; OSHW-Logo2_9.8x8mm_SilkScreen
R1, R4, R6: 47R; R_0603_1608Metric
R2: 470R; R_0603_1608Metric
R3, R5: 2k2; R_0603_1608Metric
R7, R8, R13: 10k; R_0603_1608Metric
R10, R11: 22; R_0603_1608Metric
R12: 100k; R_0603_1608Metric
U1: AMS1117-3.3; SOT-223-3_TabPin2
U2: ESP-12F; ESP-12E_SMD
U3: CH340G; MSOP-10_3x3mm_P0.5mm

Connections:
3.3V: C3.1, C4.1, R7.2, R8.1, R13.1, U1.2 (VO), U2.8 (VCC)
5V: C1.1, C2.1, J1.2, U1.3 (VI), U3.7 (VCC)
/CSEL: EXP2.7, R5.1
/D+: J3.3 (D+), R11.1
/D-: J3.2 (D-), R10.1
/DATA_RDY: EXP1.10, R13.2, U2.12 (GPIO0)
/EN: R7.1, U2.3 (CH_PD)
/E_MISO: EXP2.10, R1.1
/E_MOSI: EXP2.5, R6.1
/E_RST: EXP2.4, R2.1
/E_SCK: EXP2.9, R4.1
/MISO: R1.2, U2.6 (GPIO12)
/MOSI: R6.2, U2.7 (GPIO13)
/RST: C5.2, R2.2, U2.1 (REST)
/SCK: R4.2, U2.5 (GPIO14)
/TRF_RDY: R3.2, U2.13 (GPIO4)
/VBUS: D1.1 (K), J1.1
/VIN: EXP1.1, J1.3
GND: C1.2, C2.2, C3.2, C4.2, C5.1, C6.1, C19.1, EXP1.2, EXP2.2, J3.5 (GND), R12.1, U1.1 (GND), U2.9 (GND), U3.3 (GND)
unnamed: C6.2, U3.10 (V3)
unnamed: C19.2, J3.6 (Shield), R12.2
unnamed: D1.2 (A), F1.2
unnamed: EXP1.9, R3.1
unnamed: F1.1, J3.1 (VBUS)
unnamed: R5.2, U2.10 (GPIO15)
unnamed: R8.2, U2.11 (GPIO2)
RX: U2.15 (RXD), U3.8 (TXD)
TX: U2.16 (TXD), U3.9 (RXD)
USB_D+: R11.2, U3.1 (UD+)
USB_D-: R10.2, U3.2 (UD-)

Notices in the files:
hardware/WiFi-Addon.kicad_pcb:
(C) 2021 by Hijax_PL
